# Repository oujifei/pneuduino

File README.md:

# PneuDuino

Pneuduino is a toolkit for controlling air flow and pressure. With the sensing capability, you design robots that are soft, furniture that is adaptive, clothing that is intelligent, art pieces that are breathing, and many more things with the Pneuduino.

Disclaimer:
This toolkit is currently designed for workshops that we give. We are working on a more stable version for personal use. In the meantime, you are welcome to use what you find here - but be aware that is a work in progress.

For more information visit http://pneuduino.org/toolkit/

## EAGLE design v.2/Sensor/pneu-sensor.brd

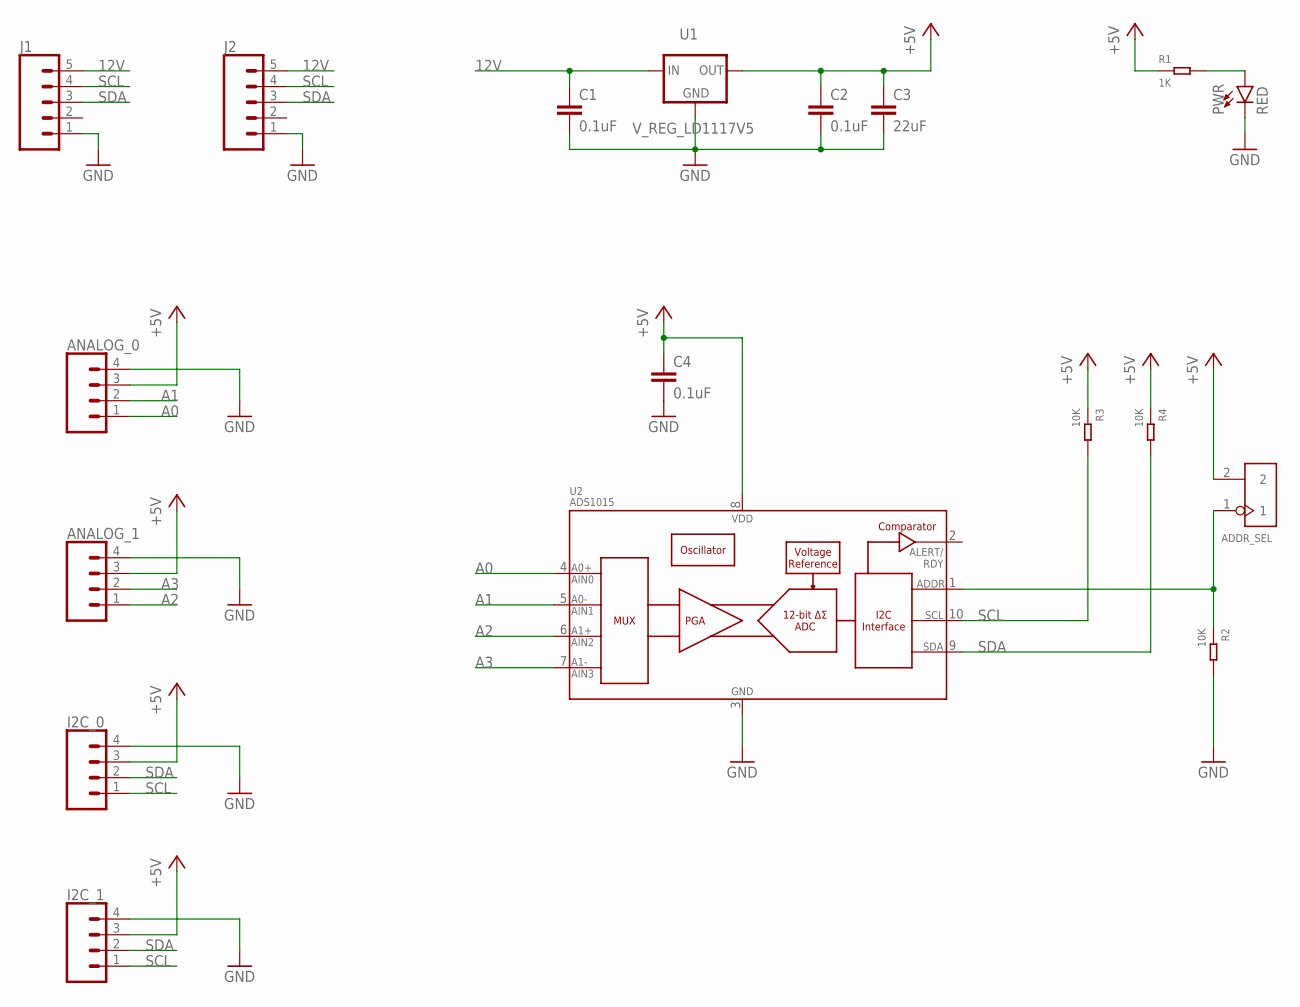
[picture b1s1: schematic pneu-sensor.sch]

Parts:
ADDR_SEL: DIP-BLACK-JUMPER; H2-2.54
ANALOG_0, ANALOG_1: CONN_04JST-PTH-VERT; JST-4-PTH-VERT
C1, C2, C4: 0.1uF; 0603
C3: 22uF; 1206
I2C_0, I2C_1: CONN_04JST-PTH-VERT; JST-4-PTH-VERT
J1, J2: CONN_05; 1X05
PWR: RED; LED-0603
R1: 1K; R0805
R2, R3, R4: 10K; R0805
U1: V_REG_LD1117V5; SOT223
U2: ADS1015; MSOP10

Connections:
12V: C1.1, J1.5, J2.5, U1.3 (IN)
+5V: ADDR_SEL.2, ANALOG_0.3, ANALOG_1.3, C2.1, C3.1, C4.1, I2C_0.3, I2C_1.3, R1.1, R3.1, R4.1, U1.2 (OUT), U1.4 (OUT), U2.8 (VDD)
A0: ANALOG_0.1, U2.4 (AIN0)
A1: ANALOG_0.2, U2.5 (AIN1)
A2: ANALOG_1.1, U2.6 (AIN2)
A3: ANALOG_1.2, U2.7 (AIN3)
GND: ANALOG_0.4, ANALOG_1.4, C1.2, C2.2, C3.2, C4.2, I2C_0.4, I2C_1.4, J1.1, J2.1, PWR.C, R2.2, U1.1 (GND), U2.3 (VSS)
unnamed: ADDR_SEL.1, R2.1, U2.1 (ADDR)
unnamed: PWR.A, R1.2
SCL: I2C_0.1, I2C_1.1, J1.4, J2.4, R3.2, U2.10 (SCL)
SDA: I2C_0.2, I2C_1.2, J1.3, J2.3, R4.2, U2.9 (SDA)

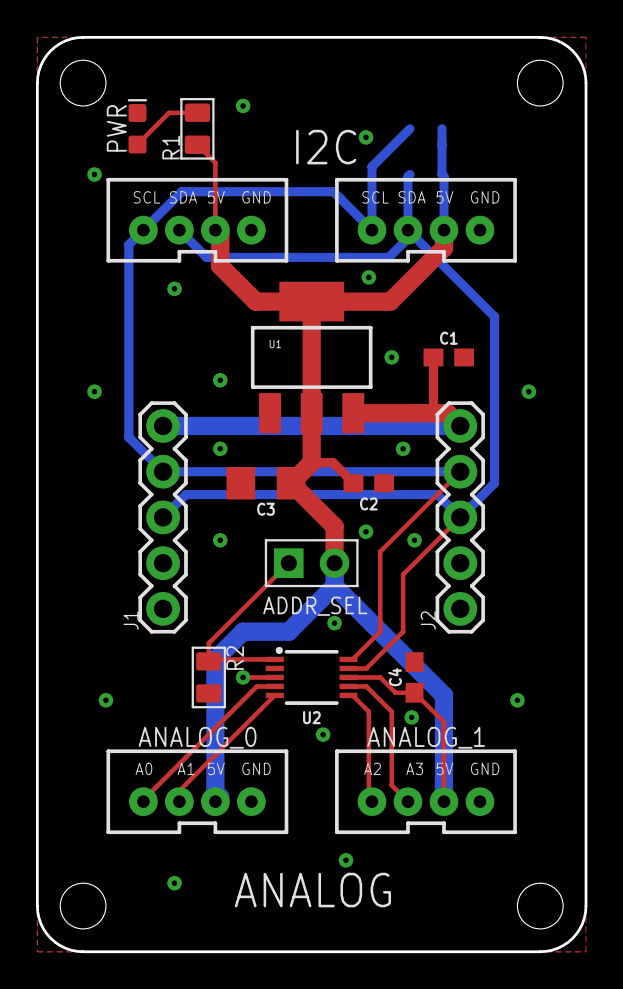
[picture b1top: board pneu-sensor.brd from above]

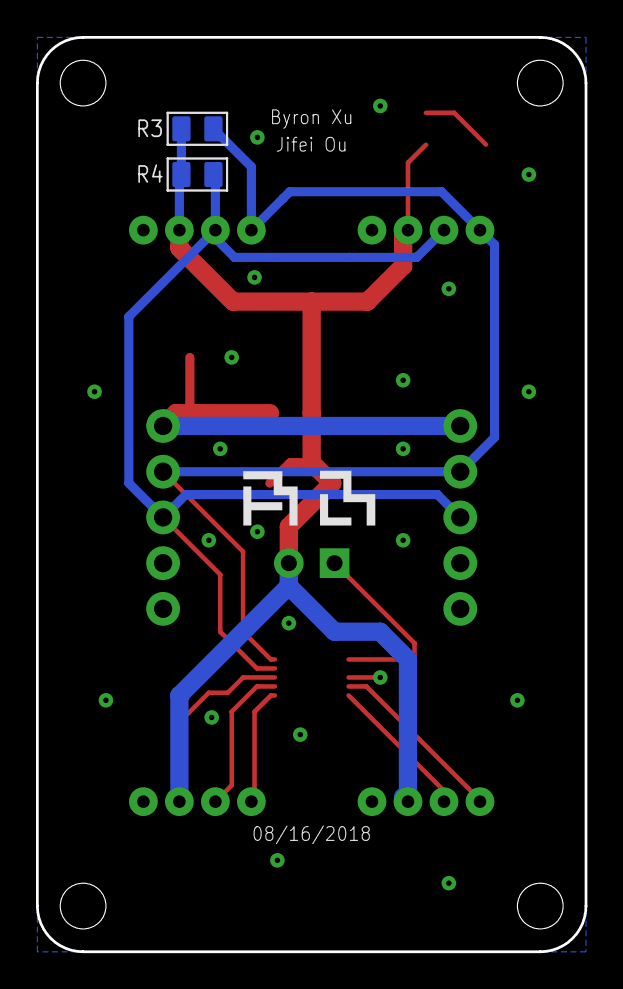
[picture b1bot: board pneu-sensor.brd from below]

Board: 2 copper layers, 30.5 x 50.8 mm, 18 parts (2 on the bottom side), 11 nets.

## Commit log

2018-06-18 added updated library and examples
2018-06-18 added images
2018-06-19 restructured readme documentation
2018-06-19 added logic gates
2018-06-19 readme links updated
2018-06-20 added documentation for logic gates
2018-06-20 added facial recognition example
2018-06-21 added LED example
2018-06-21 added LED I2C address info
2018-06-21 added haptic
2018-06-22 added wave
2018-06-22 updated wave
2018-06-22 added pressure regulation example
2018-06-22 added new examples
2018-06-24 new sensors
2018-06-25 added new sensors
2018-06-25 updated readmes
2018-06-25 added readmes for lots of sensors
2018-06-26 added GSR example
2018-06-26 added heart sensor
2018-08-07 new sensor board
2018-08-07 updated sensor board
2018-08-08 library changes
2018-08-08 added code to read adc
2018-08-09 fixed compile error
2018-08-09 removed unnecessary code
2018-08-15 ADC sensor board
2018-08-16 modified sensor board
2018-08-17 added sensor hub
2018-08-17 sensor hub readme

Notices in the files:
parts and their libraries:
SparkFun-Connectors: Licensing: Creative Commons ShareAlike 4.0 International - https://creativecommons.org/licenses/by-sa/4.0
